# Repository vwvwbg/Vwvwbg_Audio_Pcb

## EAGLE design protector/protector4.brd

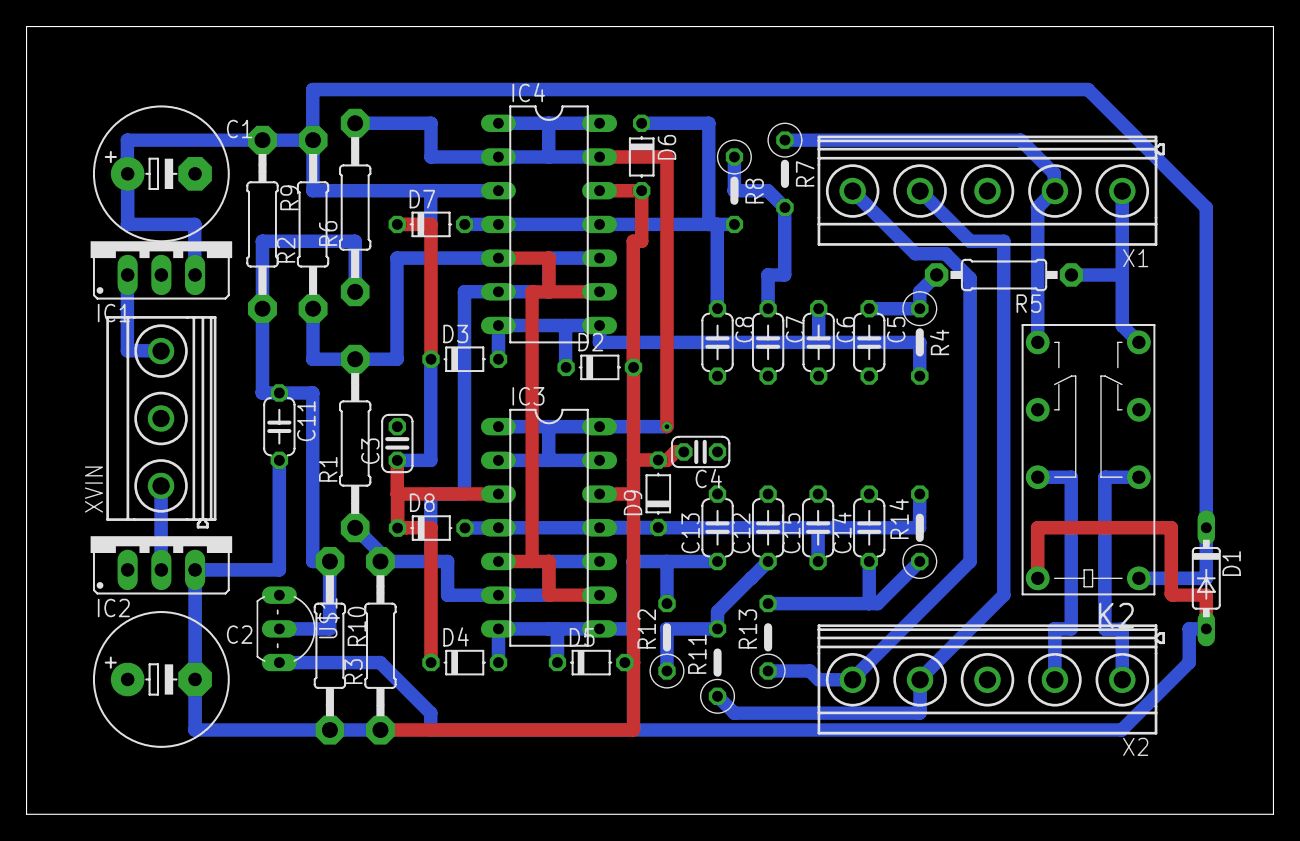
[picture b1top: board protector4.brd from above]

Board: 2 copper layers, 94.0 x 59.4 mm, 45 parts (0 on the bottom side), 24 nets.

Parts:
C1, C2: E5-10,5
C3, C4: C025-024X044
C5, C6, C7, C8, C11, C12, C13, C14, C15: C050-024X044
D1: 1N4148DO35-7; DO35-7
D2, D3, D4, D5, D6, D7, D8, D9: D-5
IC1: 78XXS
IC2: 79XXS
IC3, IC4: LM339N; DIL14
K2: G5V-2
R1: 500; 0207/12
R2, R3: 11K; 0207/12
R4, R7, R8, R11, R12, R13, R14: 100K; 0207/5V
R5: 100K; 0207/10
R6: 1K; 0207/12
R9: 100K; 0207/12
R10: 500K; 0207/12
U$1: 2N7000; TO92-
X1, X2: MKDSN1,5/5-5,08
XVIN: MKDSN1,5/3-5,08

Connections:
+12V: C1.+, C3.1, D1.C, D3.C, D4.C, D7.C, D8.C, IC1.OUT, IC3.3, IC4.3, K2.1, R2.2, R9.1
-12V: C2.-, C4.2, C11.2, D2.A, D5.A, D6.A, D9.A, IC2.OUT, IC3.12, IC4.12, R3.1, R10.2
COM+: IC3.5, IC3.9, IC4.5, IC4.9, R1.2, R2.1
COM-: IC3.6, IC3.10, IC4.6, IC4.10, R1.1, R3.2
GND: C1.-, C2.+, C3.2, C4.1, C5.2, C6.2, C7.2, C8.2, C12.2, C13.2, C14.2, C15.2, IC1.GND, IC2.GND, U$1.1, X1.3, X2.3, XVIN.2
LO+: R11.1, X1.4, X2.4
LO-: R13.1, X1.5, X2.5
unnamed: IC1.IN, XVIN.3
unnamed: IC3.1, IC3.2, IC3.13, IC3.14, IC4.1, IC4.2, IC4.13, IC4.14, R6.2
unnamed: IC2.IN, XVIN.1
unnamed: K2.8, R5.1, X1.1
unnamed: C7.1, R7.2, R8.1
unnamed: C5.1, R4.1, R5.2
unnamed: K2.9, R7.1, X1.2
unnamed: K2.13, X2.2
unnamed: C11.1, R6.1, R9.2, R10.1, U$1.2
unnamed: C6.1, D2.C, D3.A, IC4.7, IC4.8, R4.2
unnamed: C8.1, D6.C, D7.A, IC4.4, IC4.11, R8.2
unnamed: D1.A, K2.16, U$1.3
unnamed: C13.1, D4.A, D5.C, IC3.7, IC3.8, R12.2
unnamed: C15.1, D8.A, D9.C, IC3.4, IC3.11, R14.2
unnamed: K2.4, X2.1
unnamed: C12.1, R11.2, R12.1
unnamed: C14.1, R13.2, R14.1

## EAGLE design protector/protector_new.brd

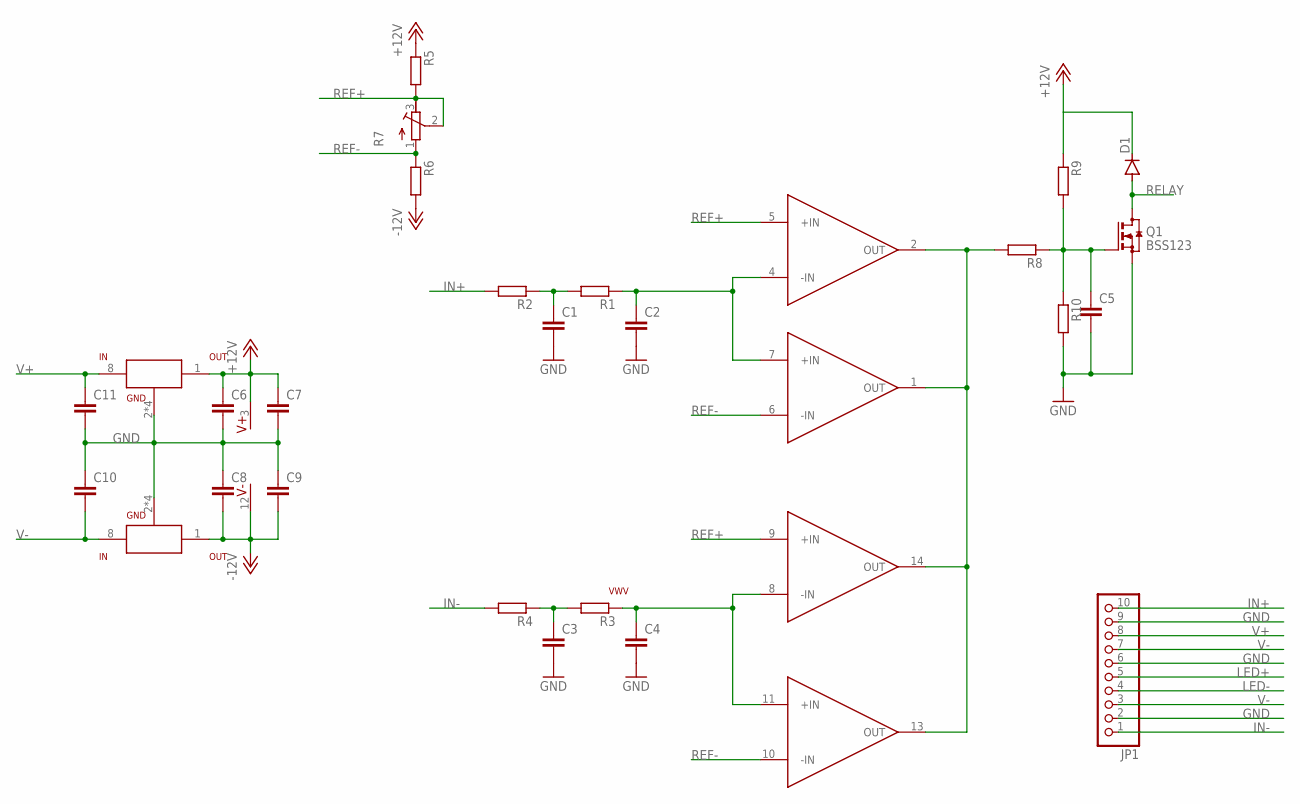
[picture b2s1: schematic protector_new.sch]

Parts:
C1, C2, C3, C4, C6, C7, C8, C9, C10, C11: C-EUC0805; C0805
C5: C-EUC1210; C1210
D1: DIODE-SOD80C; SOD80C
JP1: PINHD-1X10/90; 1X10/90
Q1: BSS123; SOT23
R1, R2, R3, R4, R5, R6, R8, R9, R10: R-EU_MELF0204W; MINI_MELF-0204W
R7: R-TRIMM3296W; RTRIM3296W
U$1: VWV
U$2: TLV1704TSSOP14; TSSOP14
U$3: MC78XXSOIC-8; SO8
U$4: MC79XXSOIC-8; SO8

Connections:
+12V: C6.1, C7.1, D1.C, R5.1, R9.1, U$2.3 (V+), U$3.1 (OUT)
-12V: C8.2, C9.2, R6.2, U$2.12 (V-), U$4.1 (OUT)
GND: C1.2, C2.2, C3.2, C4.2, C5.2, C6.2, C7.2, C8.1, C9.1, C10.1, C11.2, JP1.2, JP1.6, JP1.9, Q1.2 (S), R10.2, U$3.2 (GND), U$3.3 (GND), U$3.6 (GND), U$3.7 (GND), U$4.2 (GND), U$4.3 (GND), U$4.6 (GND), U$4.7 (GND)
IN+: JP1.10, R2.2
IN-: JP1.1, R4.2
LED+: JP1.5
LED-: JP1.4
unnamed: C2.1, R1.1, U$2.4 (-IN), U$2.7 (+IN)
unnamed: C4.1, R3.1, U$2.8 (-IN), U$2.11 (+IN)
unnamed: C1.1, R1.2, R2.1
unnamed: C5.1, Q1.1 (G), R8.1, R9.2, R10.1
unnamed: C3.1, R3.2, R4.1
unnamed: R8.2, U$2.1 (OUT), U$2.2 (OUT), U$2.13 (OUT), U$2.14 (OUT)
REF+: R5.2, R7.2 (S), R7.3 (E), U$2.5 (+IN), U$2.9 (+IN)
REF-: R6.1, R7.1 (A), U$2.6 (-IN), U$2.10 (-IN)
RELAY: D1.A, Q1.3 (D)
V+: C11.1, JP1.8, U$3.8 (IN)
V-: C10.2, JP1.3, JP1.7, U$4.8 (IN)

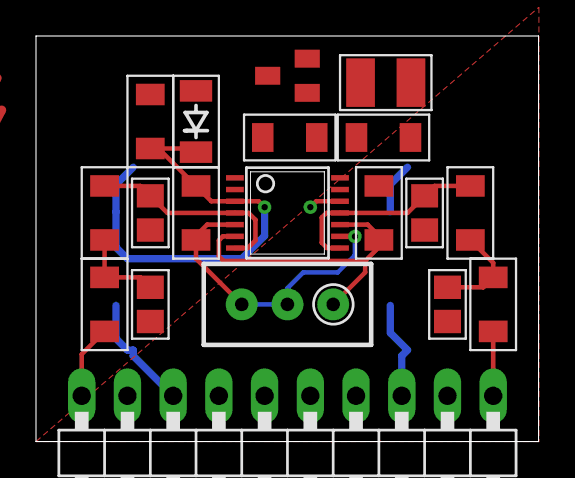
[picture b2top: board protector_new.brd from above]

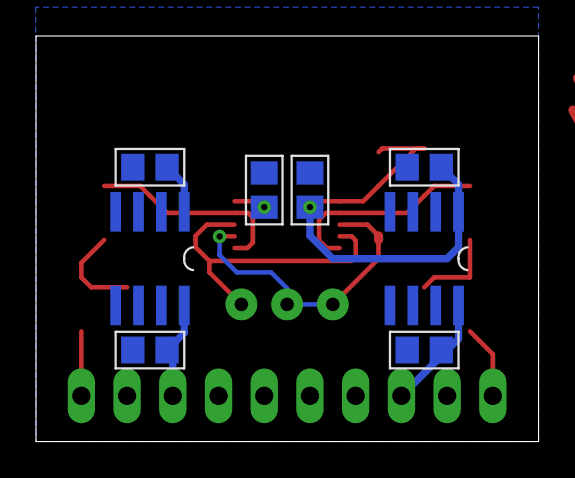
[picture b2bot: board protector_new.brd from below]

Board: 2 copper layers, 27.9 x 22.5 mm, 28 parts (8 on the bottom side), 16 nets.

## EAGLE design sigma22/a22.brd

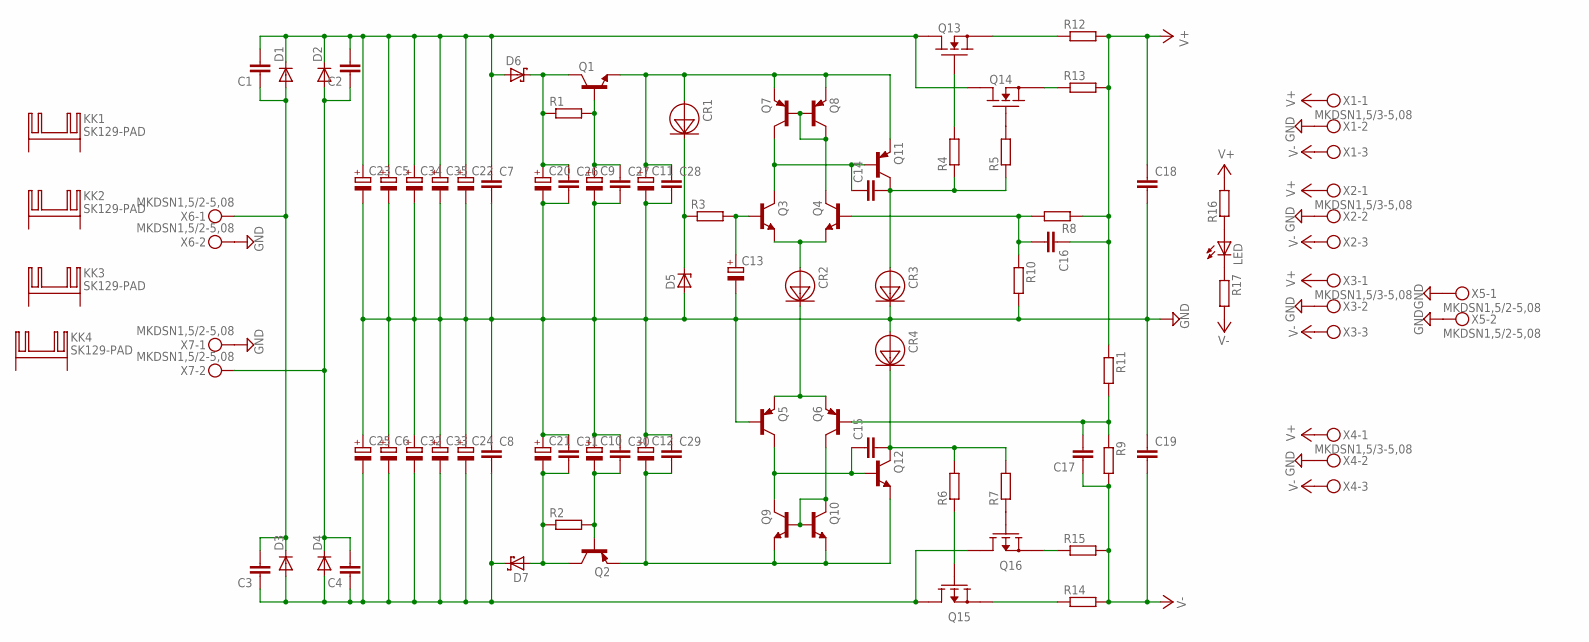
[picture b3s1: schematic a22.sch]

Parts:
C1, C2, C3, C4: C-EU025_050-025X075; C025_050-025X075
C5, C6: CPOL-EUE10-30; EB30D
C7, C8, C14, C15, C18, C19: C-EU050-075X075; C050-075X075
C9, C10, C13, C20, C21: CPOL-EUE5-10.5; E5-10,5
C11, C12: CPOL-EUE5-13; E5-13
C16, C17: C-EU025_050-045X075; C025_050-045X075
C22, C23, C24, C25, C32, C33, C34, C35: CPOL-EUE7.5-18; E7,5-18
C26, C27, C28, C29, C30, C31: C-EU050-035X075; C050-035X075
CR1, CR2, CR3, CR4: E-202; DO-35-3
D1, D2, D3, D4: MUR810; TO220ACS
D5: BZX90; DO34Z7
D6, D7: 1N5819-B; DO41-7.6
KK1, KK2, KK3, KK4: SK129-PAD; SK129
LED: LED5MM
Q1, Q3, Q4, Q9, Q10, Q12: BC550B; TO92-EBC
Q2, Q5, Q6, Q7, Q8, Q11: BC560C; TO92-EBC
Q13, Q14: IRFZ24N; TO220V
Q15, Q16: IRF9Z34N; TO220V
R1, R2, R3, R4, R5, R6, R7, R8, R9, R10, R11, R16, R17: R-EU_0309/10; 0309/10
R12, R13, R14, R15: R-EU_0617/17; 0617/17
X1, X2, X3, X4: MKDSN1,5/3-5,08
X5, X6, X7: MKDSN1,5/2-5,08

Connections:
GND: C5.-, C6.+, C7.2, C8.1, C9.-, C10.+, C11.-, C12.+, C13.-, C18.2, C19.1, C20.-, C21.+, C22.-, C23.-, C24.+, C25.+, C26.2, C27.2, C28.2, C29.1, C30.1, C31.1, C32.+, C33.+, C34.-, C35.-, CR3.1 (CATHODE), CR3.2 (CATHODE), CR3.CATHODE, CR4.ANODE, D5.A, Q5.B, R10.2, X1.2, X2.2, X3.2, X4.2, X5.1, X5.2, X6.2, X7.1
unnamed: C1.1, C3.2, C3.3 (2), D1.A, D3.C, X6.1
unnamed: C2.1, C4.2, C4.3 (2), D2.A, D4.C, X7.2
unnamed: C20.+, C26.1, D6.C, Q1.C, R1.1
unnamed: Q13.1 (G), R4.2
unnamed: C9.+, C27.1, Q1.B, R1.2
unnamed: C10.-, C30.2, Q2.B, R2.2
unnamed: C3.1, C4.1, C6.-, C8.2, C24.-, C25.-, C32.-, C33.-, D3.A, D4.A, D7.C, Q15.2 (D), Q16.2 (D)
unnamed: C21.-, C31.2, D7.A, Q2.C, R2.1
unnamed: C11.+, C28.1, CR1.ANODE, Q1.E, Q7.E, Q8.E, Q11.E
unnamed: LED.A, R16.1
unnamed: CR1.1 (CATHODE), CR1.2 (CATHODE), CR1.CATHODE, D5.C, R3.1
unnamed: C12.-, C29.2, Q2.E, Q9.E, Q10.E, Q12.E
unnamed: CR2.1 (CATHODE), CR2.2 (CATHODE), CR2.CATHODE, Q5.E, Q6.E
unnamed: CR2.ANODE, Q3.E, Q4.E
unnamed: C13.+, Q3.B, R3.2
unnamed: Q4.C, Q7.B, Q8.B, Q8.C
unnamed: Q6.C, Q9.B, Q10.B, Q10.C
unnamed: C15.1, Q5.C, Q9.C, Q12.B
unnamed: C1.2, C1.3 (2), C2.2, C2.3 (2), C5.+, C7.1, C22.+, C23.+, C34.+, C35.+, D1.C, D2.C, D6.A, Q13.2 (D), Q14.2 (D)
unnamed: C17.2, C17.3 (2), Q6.B, R9.1, R11.2
unnamed: C14.1, Q3.C, Q7.C, Q11.B
unnamed: C14.2, CR3.ANODE, Q11.C, R4.1, R5.1
unnamed: C15.2, CR4.1 (CATHODE), CR4.2 (CATHODE), CR4.CATHODE, Q12.C, R6.2, R7.2
unnamed: Q14.1 (G), R5.2
unnamed: Q16.1 (G), R7.1
unnamed: LED.K (C), R17.1
unnamed: Q15.1 (G), R6.1
unnamed: C16.2, C16.3 (2), Q4.B, R8.2, R10.1
unnamed: Q16.3 (S), R15.1
unnamed: Q15.3 (S), R14.1
unnamed: Q13.3 (S), R12.1
unnamed: Q14.3 (S), R13.1
V+: C16.1, C18.1, R8.1, R11.1, R12.2, R13.2, R16.2, X1.1, X2.1, X3.1, X4.1
V-: C17.1, C19.2, R9.2, R14.2, R15.2, R17.2, X1.3, X2.3, X3.3, X4.3

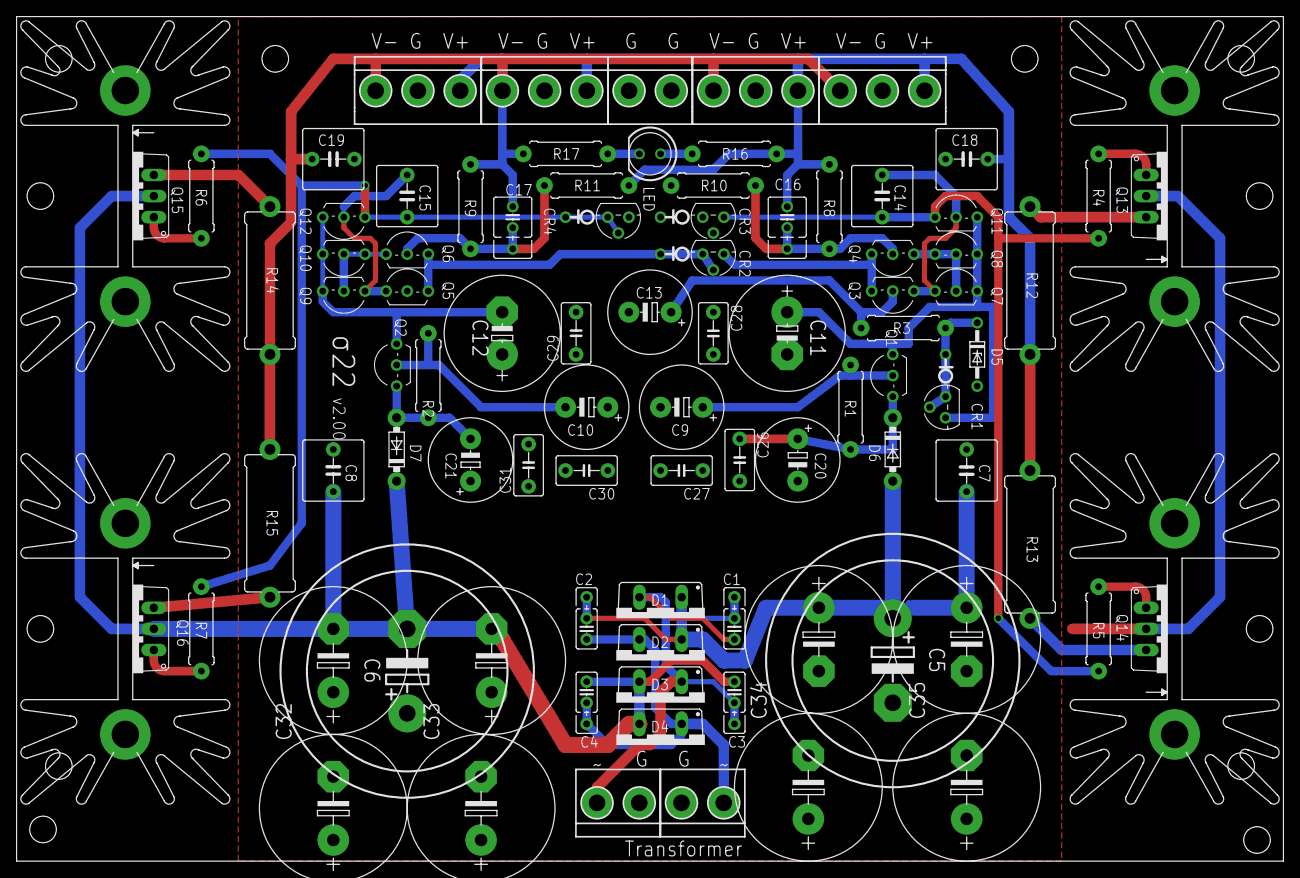
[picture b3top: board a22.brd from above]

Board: 2 copper layers, 152.4 x 101.6 mm, 91 parts (0 on the bottom side), 35 nets.

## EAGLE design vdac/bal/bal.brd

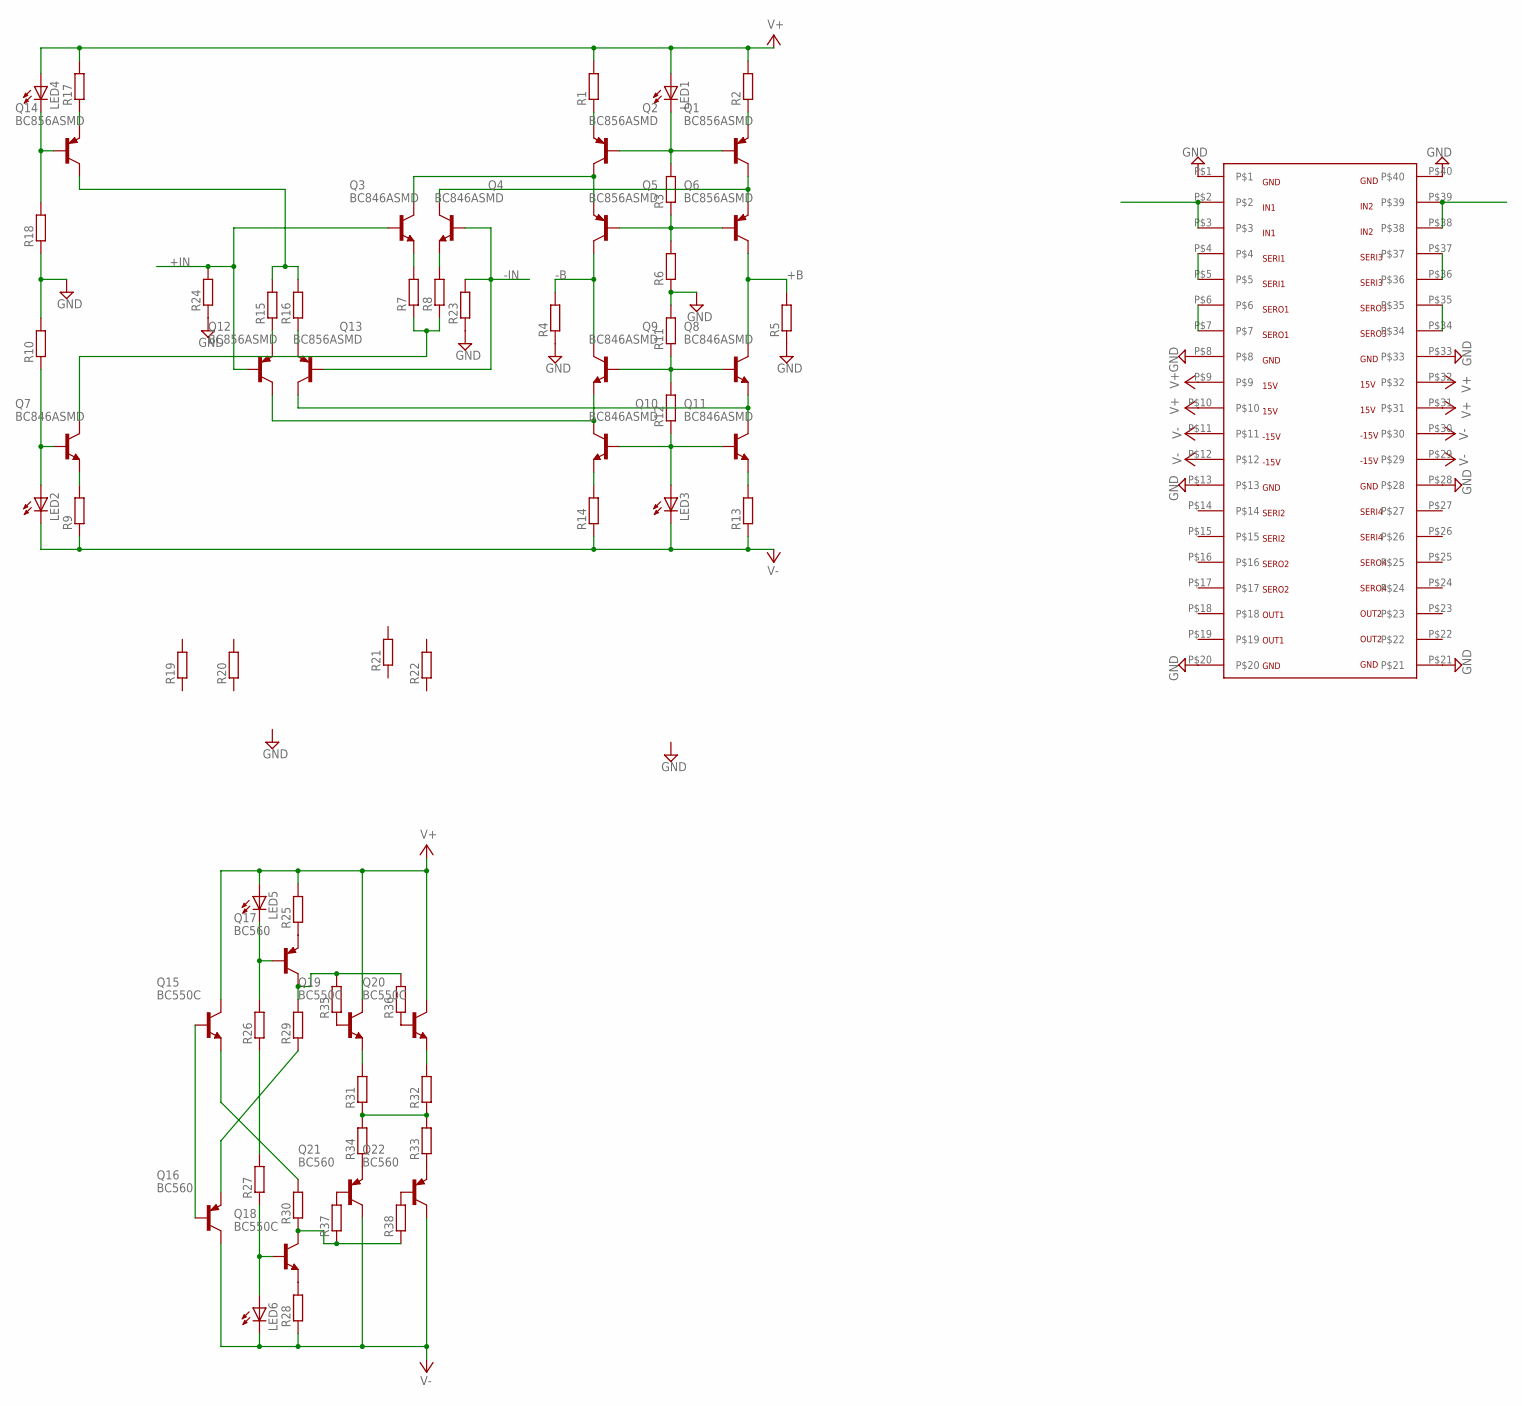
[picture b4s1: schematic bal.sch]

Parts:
LED1, LED2, LED3, LED4, LED5, LED6: LED5MM
Q1, Q2, Q5, Q6, Q12, Q13, Q14: BC856ASMD; SOT23-BEC
Q3, Q4, Q7, Q8, Q9, Q10, Q11: BC846ASMD; SOT23
Q15, Q18, Q19, Q20: BC550C; TO92-EBC
Q16, Q17, Q21, Q22: BC560; TO92_1
R1, R2, R3, R4, R5, R6, R7, R8, R9, R10, R11, R12, R13, R14, R15, R16, R17, R18, R19, R20, R21, R22, R23, R24, R25, R26, R27, R28, R29, R30, R31, R32, R33, R34, R35, R36, R37, R38: R-EU_MELF0204W; MINI_MELF-0204W
U$1: VDACA

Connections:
+B: Q6.C, Q8.3 (C), R5.2
+IN: Q3.1 (B), Q12.B, R24.2, U$1.P$2, U$1.P$3
-B: Q5.C, Q9.3 (C), R4.2
-IN: Q4.1 (B), Q13.B, R23.2, U$1.P$38, U$1.P$39
GND: R4.1, R5.1, R6.1, R10.2, R11.2, R18.1, R23.1, R24.1, U$1.P$1, U$1.P$8, U$1.P$13, U$1.P$20, U$1.P$21, U$1.P$28, U$1.P$33, U$1.P$40
unnamed: U$1.P$4, U$1.P$5
unnamed: Q1.E, R2.1
unnamed: Q2.E, R1.1
unnamed: LED1.K (C), Q1.B, Q2.B, R3.2
unnamed: Q5.B, Q6.B, R3.1, R6.2
unnamed: Q1.C, Q4.3 (C), Q6.E
unnamed: Q2.C, Q3.3 (C), Q5.E
unnamed: Q8.1 (B), Q9.1 (B), R11.1, R12.2
unnamed: U$1.P$36, U$1.P$37
unnamed: U$1.P$6, U$1.P$7
unnamed: U$1.P$34, U$1.P$35
unnamed: Q9.2 (E), Q10.3 (C), Q12.C
unnamed: LED3.A, Q10.1 (B), Q11.1 (B), R12.1
unnamed: Q8.2 (E), Q11.3 (C), Q13.C
unnamed: Q16.3 (E), R29.1
unnamed: Q10.2 (E), R14.2
unnamed: Q11.2 (E), R13.2
unnamed: Q4.2 (E), R8.2
unnamed: Q3.2 (E), R7.2
unnamed: Q7.3 (C), R7.1, R8.1
unnamed: Q14.E, R17.1
unnamed: LED4.K (C), Q14.B, R18.2
unnamed: Q7.2 (E), R9.2
unnamed: Q14.C, R15.2, R16.2
unnamed: LED2.A, Q7.1 (B), R10.1
unnamed: LED5.K (C), Q17.2 (B), R26.2
unnamed: Q13.E, R16.1
unnamed: Q12.E, R15.1
unnamed: Q17.3 (E), R25.1
unnamed: R26.1, R27.2
unnamed: Q15.E, R30.2
unnamed: LED6.A, Q18.B, R27.1
unnamed: Q18.E, R28.2
unnamed: Q17.1 (C), R29.2, R35.2, R36.2
unnamed: Q18.C, R30.1, R37.1, R38.1
unnamed: Q15.B, Q16.2 (B)
unnamed: Q19.E, R31.2
unnamed: Q20.E, R32.2
unnamed: Q22.3 (E), R33.1
unnamed: Q21.3 (E), R34.1
unnamed: Q21.2 (B), R37.2
unnamed: R31.1, R32.1, R33.2, R34.2
unnamed: Q19.B, R35.1
unnamed: Q20.B, R36.1
unnamed: Q22.2 (B), R38.2
V+: LED1.A, LED4.A, LED5.A, Q15.C, Q19.C, Q20.C, R1.2, R2.2, R17.2, R25.2, U$1.P$9, U$1.P$10, U$1.P$31, U$1.P$32
V-: LED2.K (C), LED3.K (C), LED6.K (C), Q16.1 (C), Q21.1 (C), Q22.1 (C), R9.1, R13.1, R14.1, R28.1, U$1.P$11, U$1.P$12, U$1.P$29, U$1.P$30

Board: 2 copper layers, 67 parts (0 on the bottom side), 52 nets, no tracks yet.

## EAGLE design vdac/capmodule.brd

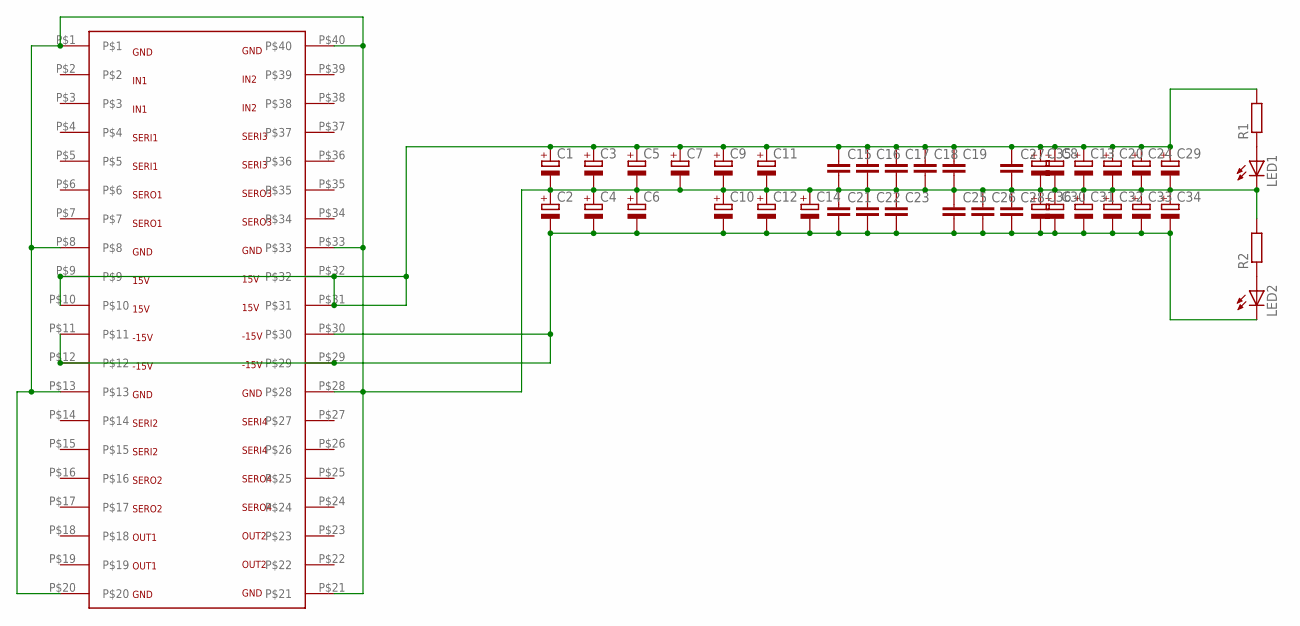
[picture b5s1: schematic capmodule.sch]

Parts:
C1, C2, C3, C4, C5, C6, C7, C9, C10, C11, C12, C14: CPOL-EUE3.5-8; E3,5-8
C8, C13, C20, C24, C29, C30, C31, C32, C33, C34, C35, C36: CPOL-EUSP-CAP-CX; SP-CAP-CX
C15, C16, C17, C18, C19, C21, C22, C23, C25, C26, C27, C28: C-EU050-035X075; C050-035X075
LED1, LED2: LEDSML1206; SML1206
R1, R2: R-EU_MELF0204W; MINI_MELF-0204W
U$1: VDACA

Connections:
15V: C1.+, C3.+, C5.+, C7.+, C8.+, C9.+, C11.+, C13.+, C15.1, C16.1, C17.1, C18.1, C19.1, C20.+, C24.+, C27.1, C29.+, C35.+, R1.2, U$1.P$9, U$1.P$10, U$1.P$31, U$1.P$32
-15V: C2.-, C4.-, C6.-, C10.-, C12.-, C14.-, C21.2, C22.2, C23.2, C25.2, C26.2, C28.2, C30.-, C31.-, C32.-, C33.-, C34.-, C36.-, LED2.C, U$1.P$11, U$1.P$12, U$1.P$29, U$1.P$30
GND: C1.-, C2.+, C3.-, C4.+, C5.-, C6.+, C7.-, C8.-, C9.-, C10.+, C11.-, C12.+, C13.-, C14.+, C15.2, C16.2, C17.2, C18.2, C19.2, C20.-, C21.1, C22.1, C23.1, C24.-, C25.1, C26.1, C27.2, C28.1, C29.-, C30.+, C31.+, C32.+, C33.+, C34.+, C35.-, C36.+, LED1.C, R2.2, U$1.P$1, U$1.P$8, U$1.P$13, U$1.P$20, U$1.P$21, U$1.P$28, U$1.P$33, U$1.P$40
unnamed: LED1.A, R1.1
unnamed: LED2.A, R2.1

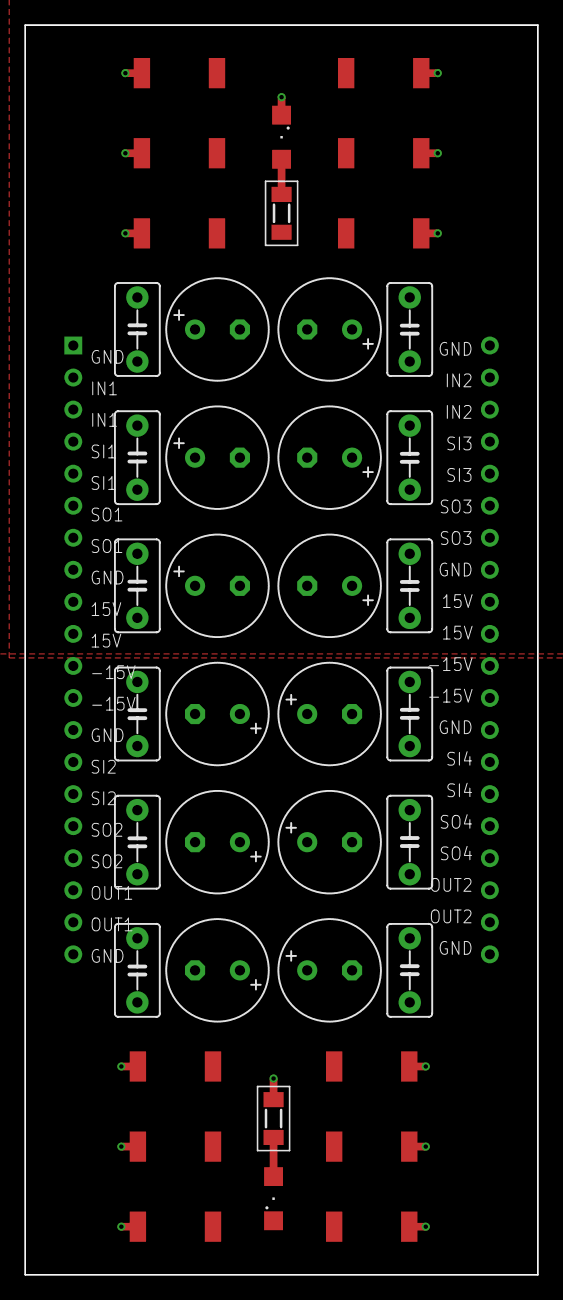
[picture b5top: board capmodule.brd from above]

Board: 2 copper layers, 40.6 x 99.0 mm, 41 parts (0 on the bottom side), 5 nets.

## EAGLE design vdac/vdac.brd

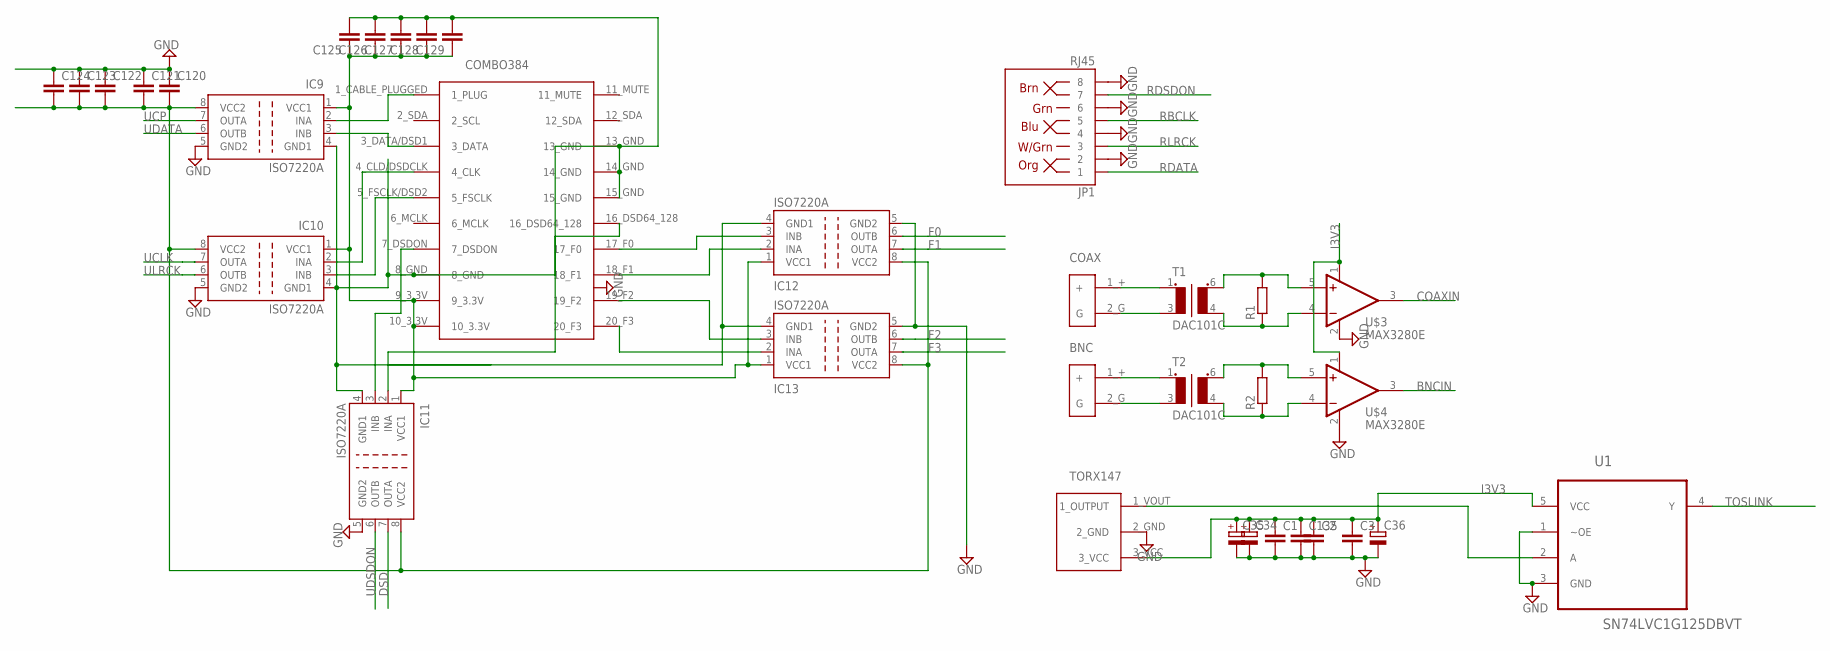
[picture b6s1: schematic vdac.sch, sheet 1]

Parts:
BNC: RCA
C1, C2, C3, C120, C121, C122, C123, C124, C125, C126, C127, C128, C129, C135: C-EUC0805; C0805
C34, C35, C36: CPOL-EUSP-CAP-CX; SP-CAP-CX
COAX: RCA
IC9, IC10, IC11, IC12, IC13: ISO7220A; SO-08
JP1: RJ45; RJ45-8
R1, R2: R-EU_MELF0204W; MINI_MELF-0204W
T1, T2: DAC101C; DAC101
U1: SN74LVC1G125DBVT; SOT95P280X145-5N
U$1: COMBO384
U$2: TORX147
U$3, U$4: MAX3280E; SOT23-5L

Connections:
BNCIN: U$4.3 (OUT); also elsewhere on the board
COAXIN: U$3.3 (OUT); also elsewhere on the board
DSD: IC11.7 (OUTA); also elsewhere on the board
F0: IC12.6 (OUTB); also elsewhere on the board
F1: IC12.7 (OUTA); also elsewhere on the board
F2: IC13.6 (OUTB); also elsewhere on the board
F3: IC13.7 (OUTA); also elsewhere on the board
GND: C1.2, C2.2, C3.2, C34.-, C35.-, C36.-, C120.1, C121.1, C122.1, C123.1, C124.1, C135.2, IC9.5 (GND2), IC10.5 (GND2), IC11.5 (GND2), IC12.5 (GND2), IC13.5 (GND2), JP1.2, JP1.4, JP1.6, JP1.8, U1.1 (~OE), U1.3 (GND), U$2.2_GND, U$3.2 (V-), U$4.2 (V-); also elsewhere on the board
I3V3: C1.1, C2.1, C3.1, C34.+, C35.+, C36.+, C120.2, C121.2, C122.2, C123.2, C124.2, C135.1, IC9.8 (VCC2), IC10.8 (VCC2), IC11.8 (VCC2), IC12.8 (VCC2), IC13.8 (VCC2), U1.5 (VCC), U$2.3_VCC, U$3.1 (V+), U$4.1 (V+); also elsewhere on the board
unnamed: COAX.1_+ (+), T1.1
unnamed: COAX.2_G (G), T1.3 (P2)
unnamed: BNC.1_+ (+), T2.1
unnamed: BNC.2_G (G), T2.3 (P2)
unnamed: R1.2, T1.6 (S1), U$3.5 (+IN)
unnamed: R1.1, T1.4 (S2), U$3.4 (-IN)
unnamed: R2.2, T2.6 (S1), U$4.5 (+IN)
unnamed: R2.1, T2.4 (S2), U$4.4 (-IN)
unnamed: U1.2 (A), U$2.1_VOUT (1_OUTPUT)
unnamed: IC9.2 (INA), U$1.1_CABLE_PLUGGED (1_PLUG)
unnamed: IC9.3 (INB), U$1.3_DATA/DSD1 (3_DATA)
unnamed: IC10.2 (INA), U$1.4_CLD/DSDCLK (4_CLK)
unnamed: IC10.3 (INB), U$1.5_FSCLK/DSD2 (5_FSCLK)
unnamed: IC11.3 (INB), U$1.7_DSDON
unnamed: C125.1, C126.1, C127.1, C128.1, C129.1, IC9.1 (VCC1), IC10.1 (VCC1), IC11.1 (VCC1), IC12.1 (VCC1), IC13.1 (VCC1), U$1.9_3.3V, U$1.10_3.3V
unnamed: IC11.2 (INA), U$1.16_DSD64_128
unnamed: IC12.3 (INB), U$1.17_F0
unnamed: IC12.2 (INA), U$1.18_F1
unnamed: IC13.3 (INB), U$1.19_F2
unnamed: IC13.2 (INA), U$1.20_F3
RBCLK: JP1.5; also elsewhere on the board
RDATA: JP1.1; also elsewhere on the board
RDSDON: JP1.7; also elsewhere on the board
RLRCK: JP1.3; also elsewhere on the board
TOSLINK: U1.4 (Y); also elsewhere on the board
UCLK: IC10.7 (OUTA); also elsewhere on the board
UCP: IC9.7 (OUTA)
UDATA: IC9.6 (OUTB); also elsewhere on the board
UDSDON: IC11.6 (OUTB); also elsewhere on the board
UGND: C125.2, C126.2, C127.2, C128.2, C129.2, IC9.4 (GND1), IC10.4 (GND1), IC11.4 (GND1), IC12.4 (GND1), IC13.4 (GND1), U$1.8_GND, U$1.13_GND, U$1.14_GND, U$1.15_GND
ULRCK: IC10.6 (OUTB); also elsewhere on the board

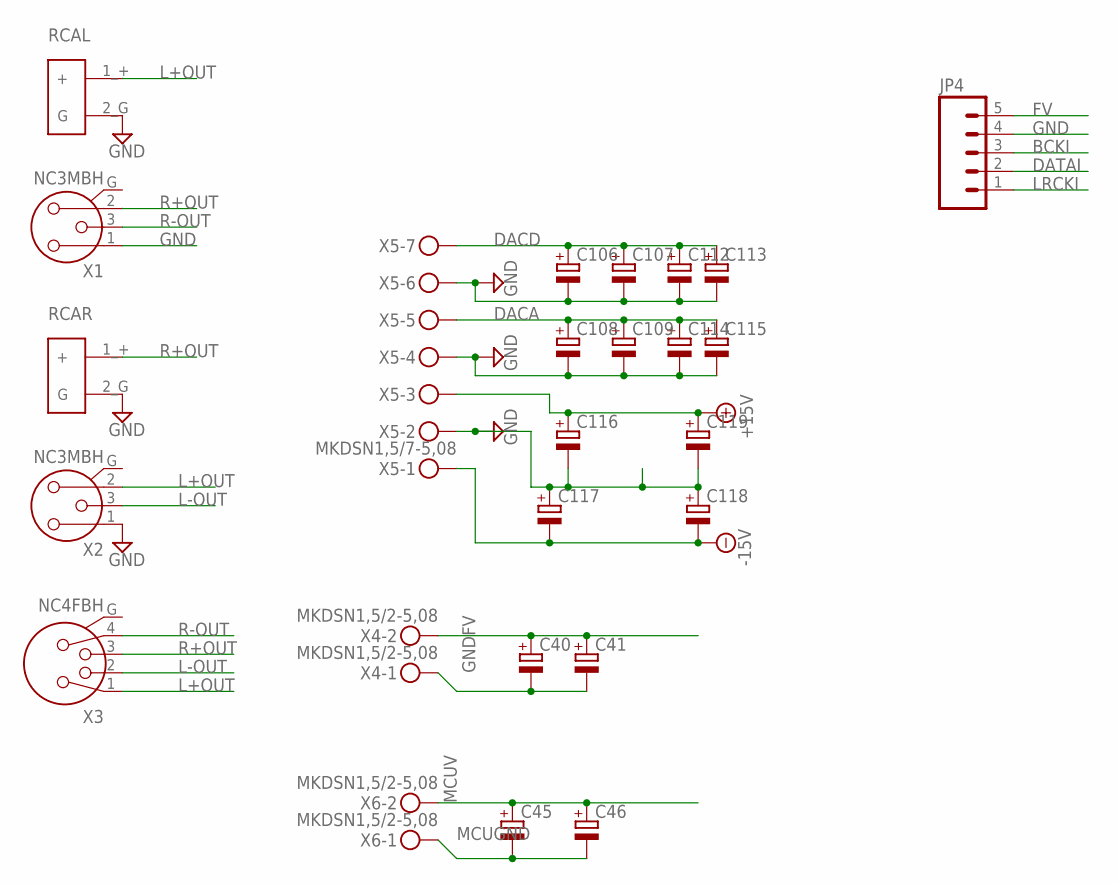
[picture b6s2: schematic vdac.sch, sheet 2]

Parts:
C40, C41, C45, C46, C106, C107, C108, C109, C112, C113, C114, C115, C116, C117, C118, C119: CPOL-EUSP-CAP-CX; SP-CAP-CX
JP4: M05PTH_LONGPADS; 1X05_LONGPADS
RCAL: RCA
RCAR: RCA
X1, X2: NC3MBH
X3: NC4FBH
X4, X6: MKDSN1,5/2-5,08
X5: MKDSN1,5/7-5,08

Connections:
+15V: C116.+, C119.+, X5.3; also elsewhere on the board
-15V: C117.-, C118.-, X5.1; also elsewhere on the board
BCKI: JP4.3; also elsewhere on the board
DACA: C108.+, C109.+, C114.+, C115.+, X5.5; also elsewhere on the board
DACD: C106.+, C107.+, C112.+, C113.+, X5.7; also elsewhere on the board
DATAI: JP4.2; also elsewhere on the board
FV: C40.+, C41.+, JP4.5, X4.2; also elsewhere on the board
GND: C40.-, C41.-, C106.-, C107.-, C108.-, C109.-, C112.-, C113.-, C114.-, C115.-, C116.-, C117.+, C118.+, C119.-, JP4.4, RCAL.2_G (G), RCAR.2_G (G), X1.1, X2.1, X4.1, X5.2, X5.4, X5.6; also elsewhere on the board
L+OUT: RCAL.1_+ (+), X2.2, X3.1; also elsewhere on the board
L-OUT: X2.3, X3.2; also elsewhere on the board
LRCKI: JP4.1; also elsewhere on the board
MCUGND: C45.-, C46.-, X6.1; also elsewhere on the board
MCUV: C45.+, C46.+, X6.2; also elsewhere on the board
R+OUT: RCAR.1_+ (+), X1.2, X3.3; also elsewhere on the board
R-OUT: X1.3, X3.4; also elsewhere on the board

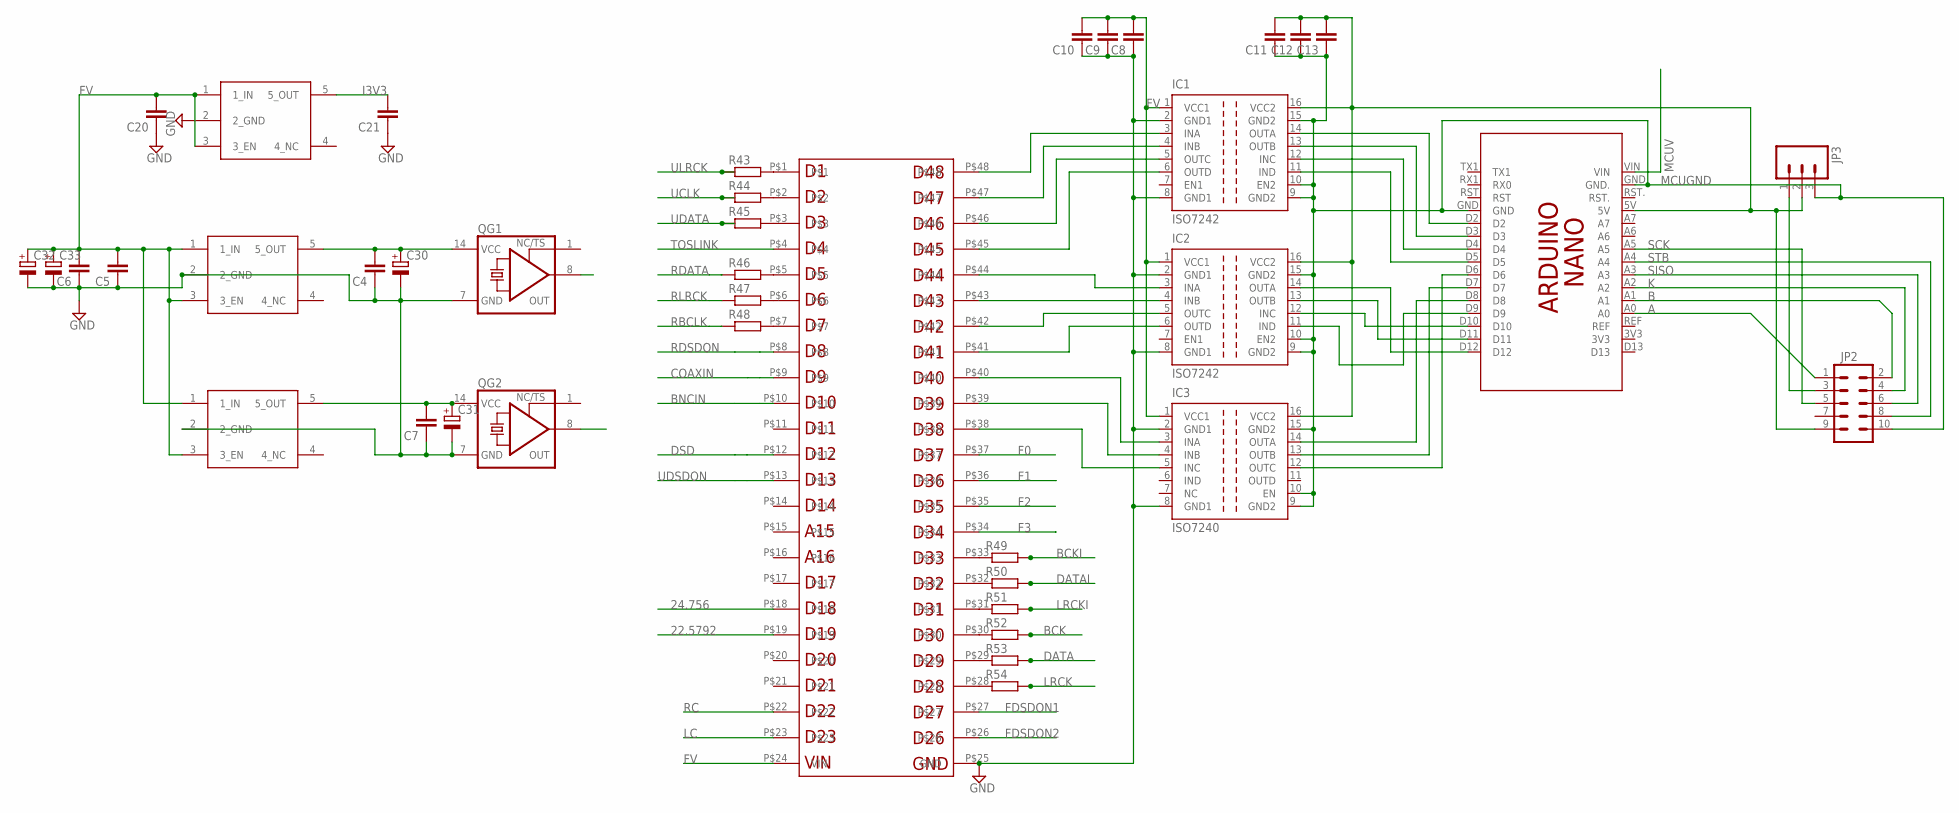
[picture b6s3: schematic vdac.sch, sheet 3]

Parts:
C4, C5, C6, C7, C8, C9, C10, C11, C12, C13, C20, C21: C-EUC0805; C0805
C30, C31, C32, C33: CPOL-EUSP-CAP-CX; SP-CAP-CX
IC1, IC2: ISO7242; SO-16DW
IC3: ISO7240; SO-16DW
JP2: M05X2SHD; 2X5-SHROUDED
JP3: M03JST-PTH-VERT; JST-3-PTH-VERT
PCB1: ARDUINO_NANO
QG1, QG2: XO-14; DIL14S
R43, R44, R45, R46, R47, R48, R49, R50, R51, R52, R53, R54: R-EU_MELF0204W; MINI_MELF-0204W
U$10, U$15, U$16: LP5907; SOT-23-5
U$12: CMOD-A7; CMODA7

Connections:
22.5792: QG2.8 (OUT), U$12.P$19
24.756: QG1.8 (OUT), U$12.P$18
A: JP2.1, PCB1.A0
B: JP2.2, PCB1.A1
BCK: R52.2; also elsewhere on the board
BCKI: R49.2; also elsewhere on the board
BNCIN: U$12.P$10; also elsewhere on the board
COAXIN: U$12.P$9; also elsewhere on the board
D2: IC1.14 (OUTA), PCB1.D2
D3: IC1.13 (OUTB), PCB1.D3
D4: IC1.12 (INC), PCB1.D4
D5: IC1.11 (IND), PCB1.D5
DATA: R53.2; also elsewhere on the board
DATAI: R50.2; also elsewhere on the board
DSD: U$12.P$12; also elsewhere on the board
F0: U$12.P$37; also elsewhere on the board
F1: U$12.P$36; also elsewhere on the board
F2: U$12.P$35; also elsewhere on the board
F3: U$12.P$34; also elsewhere on the board
FDSDON1: U$12.P$27; also elsewhere on the board
FDSDON2: U$12.P$26; also elsewhere on the board
FV: C5.2, C6.2, C8.2, C9.2, C10.2, C20.2, C32.+, C33.+, IC1.1 (VCC1), IC2.1 (VCC1), IC3.1 (VCC1), U$10.1 (1_IN), U$10.3 (3_EN), U$12.P$24 (VIN), U$15.1 (1_IN), U$15.3 (3_EN), U$16.1 (1_IN), U$16.3 (3_EN); also elsewhere on the board
GND: C4.1, C5.1, C6.1, C7.1, C8.1, C9.1, C10.1, C20.1, C21.1, C30.-, C31.-, C32.-, C33.-, IC1.2 (GND1), IC1.8 (GND1), IC2.2 (GND1), IC2.8 (GND1), IC3.2 (GND1), IC3.8 (GND1), QG1.7 (GND), QG2.7 (GND), U$10.2 (2_GND), U$12.P$25 (GND), U$15.2 (2_GND), U$16.2 (2_GND); also elsewhere on the board
I3V3: C21.2, U$10.5 (5_OUT); also elsewhere on the board
K: JP2.4, PCB1.A2
LC: U$12.P$23; also elsewhere on the board
LRCK: R54.2; also elsewhere on the board
LRCKI: R51.2; also elsewhere on the board
MCUGND: C11.1, C12.1, C13.1, IC1.9 (GND2), IC1.10 (EN2), IC1.15 (GND2), IC2.9 (GND2), IC2.10 (EN2), IC2.15 (GND2), IC3.9 (GND2), IC3.10 (EN), IC3.15 (GND2), JP2.10, JP3.3, PCB1.GND, PCB1.GND.; also elsewhere on the board
MCUV: PCB1.VIN; also elsewhere on the board
unnamed: R43.2, U$12.P$1
unnamed: C4.2, C30.+, QG1.14 (VCC), U$15.5 (5_OUT)
unnamed: C7.2, C31.+, QG2.14 (VCC), U$16.5 (5_OUT)
unnamed: IC1.3 (INA), U$12.P$48
unnamed: IC1.4 (INB), U$12.P$47
unnamed: IC1.5 (OUTC), U$12.P$46
unnamed: IC1.6 (OUTD), U$12.P$45
unnamed: IC2.3 (INA), U$12.P$44
unnamed: IC2.4 (INB), U$12.P$43
unnamed: IC2.5 (OUTC), U$12.P$42
unnamed: IC2.6 (OUTD), U$12.P$41
unnamed: IC3.3 (INA), U$12.P$40
unnamed: IC3.4 (INB), U$12.P$39
unnamed: IC3.5 (INC), U$12.P$38
unnamed: IC2.14 (OUTA), PCB1.D12
unnamed: IC2.13 (OUTB), PCB1.D11
unnamed: IC2.12 (INC), PCB1.D10
unnamed: IC2.11 (IND), PCB1.D9
unnamed: IC3.14 (OUTA), PCB1.D8
unnamed: IC3.13 (OUTB), PCB1.D7
unnamed: IC3.12 (OUTC), PCB1.D6
unnamed: C11.2, C12.2, C13.2, IC1.16 (VCC2), IC2.16 (VCC2), IC3.16 (VCC2), JP2.9, JP3.2, PCB1.5V
unnamed: JP2.3, JP3.1
unnamed: R44.2, U$12.P$2
unnamed: R45.2, U$12.P$3
unnamed: R46.2, U$12.P$5
unnamed: R47.2, U$12.P$6
unnamed: R48.2, U$12.P$7
unnamed: R49.1, U$12.P$33
unnamed: R50.1, U$12.P$32
unnamed: R51.1, U$12.P$31
unnamed: R52.1, U$12.P$30
unnamed: R53.1, U$12.P$29
unnamed: R54.1, U$12.P$28
RBCLK: R48.1; also elsewhere on the board
RC: U$12.P$22; also elsewhere on the board
RDATA: R46.1; also elsewhere on the board
RDSDON: U$12.P$8; also elsewhere on the board
RLRCK: R47.1; also elsewhere on the board
SCK: JP2.5, PCB1.A5
SISO: JP2.6, PCB1.A3
STB: JP2.8, PCB1.A4
TOSLINK: U$12.P$4; also elsewhere on the board
UCLK: R44.1; also elsewhere on the board
UDATA: R45.1; also elsewhere on the board
UDSDON: U$12.P$13; also elsewhere on the board
ULRCK: R43.1; also elsewhere on the board

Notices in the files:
parts and their libraries:
SparkFun-Connectors: Licensing: Creative Commons ShareAlike 4.0 International - https://creativecommons.org/licenses/by-sa/4.0
